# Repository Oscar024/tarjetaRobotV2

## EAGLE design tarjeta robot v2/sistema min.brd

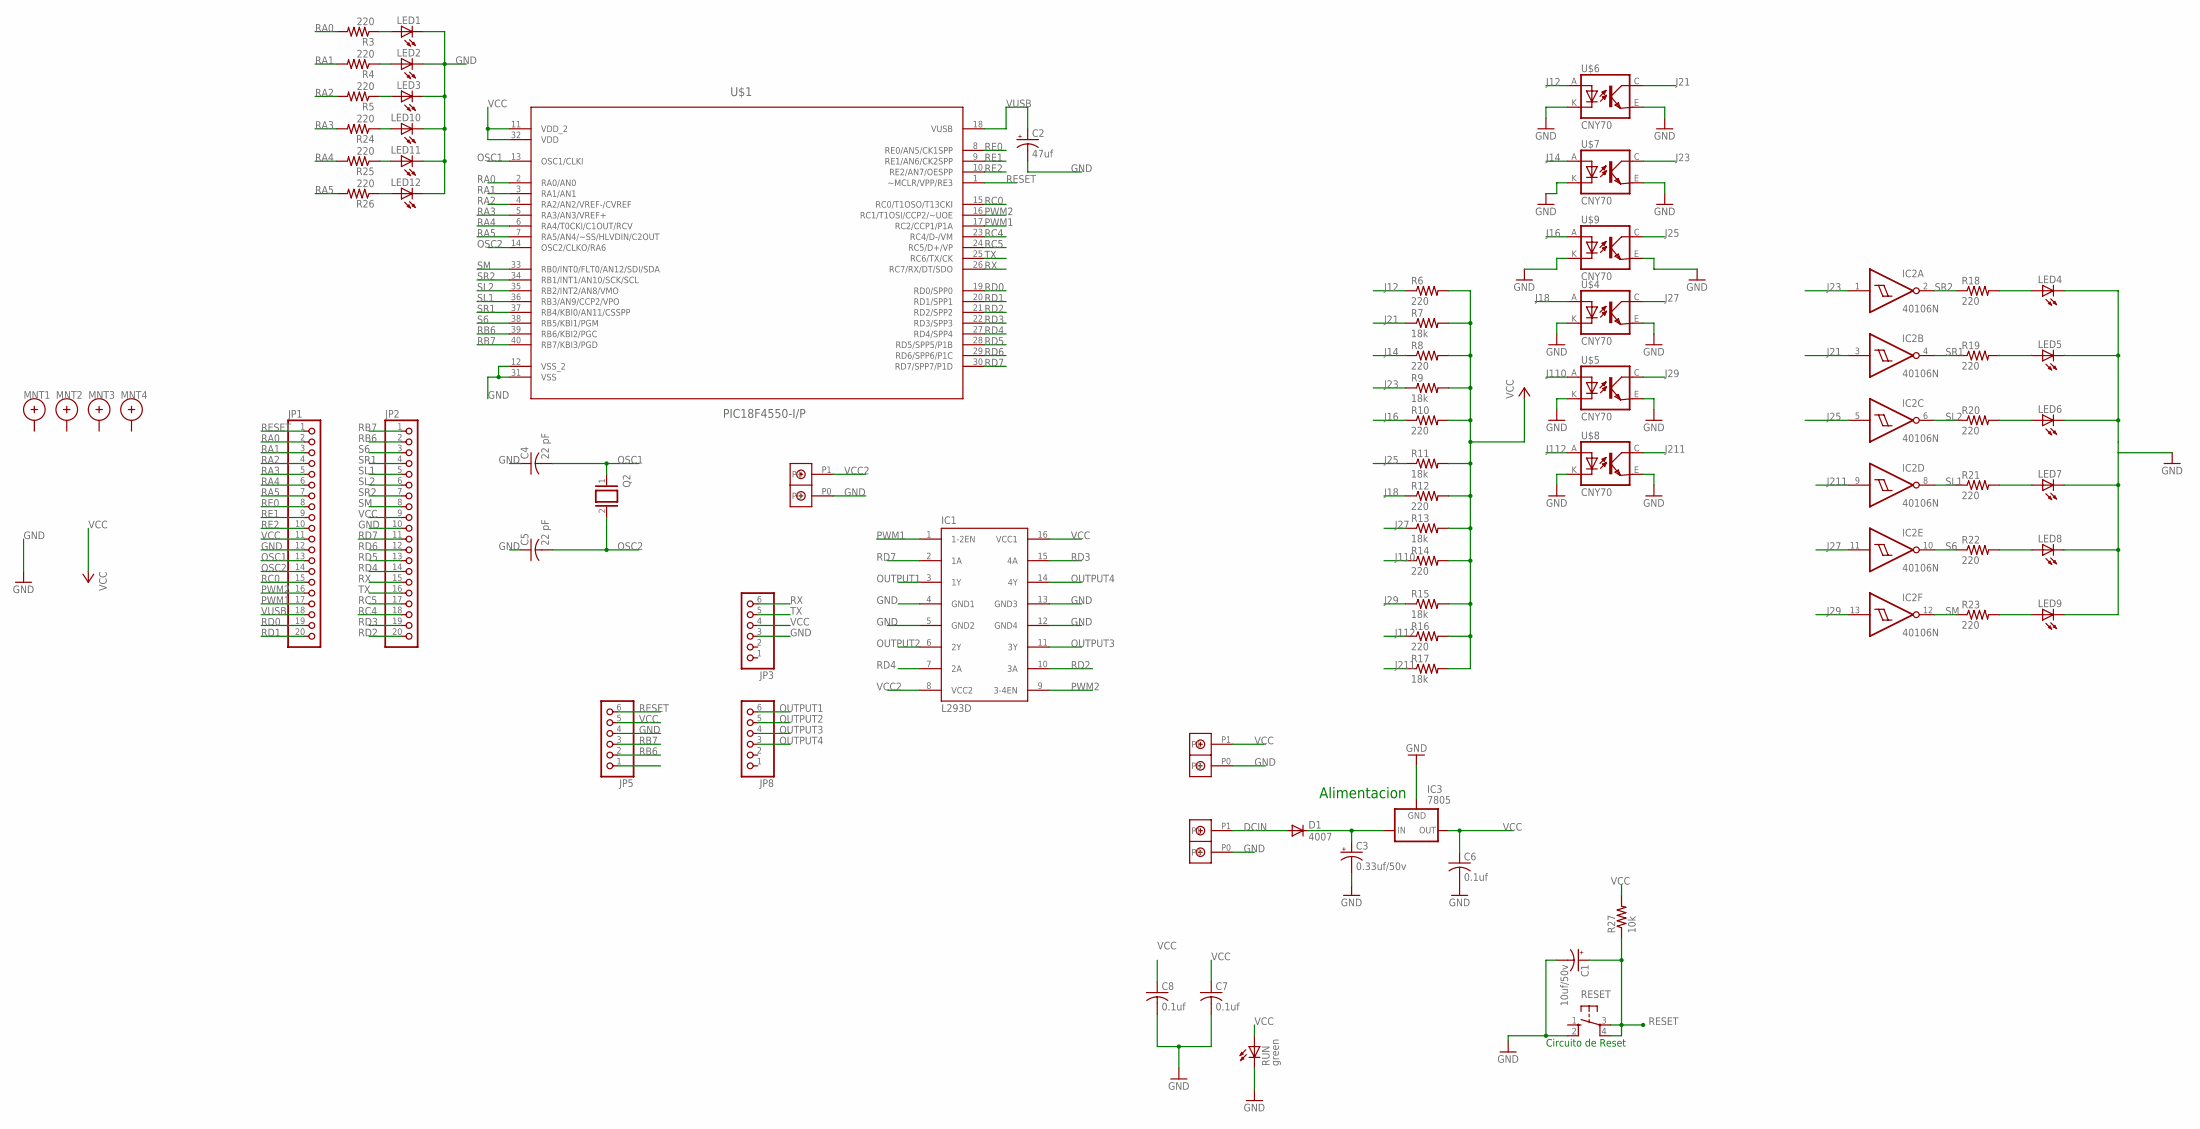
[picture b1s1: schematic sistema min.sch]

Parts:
C1: 10uf/50v; 153CLV-0505
C2: 47uf; 153CLV-0605
C3: 0.33uf/50v; 153CLV-0405
C4, C5: 22 pF; C1206
C6, C7, C8: 0.1uf; C1206
D1: 4007; DO35-7
IC1: L293D; DIL16
IC2: 40106N; DIL14
IC3: 7805; 79XXS
JP1, JP2: PINHD-1X20; 1X20
JP3, JP5, JP8: PINHD-1X6; 1X06
LED1, LED2, LED3, LED4, LED5, LED6, LED7, LED8, LED9, LED10, LED11, LED12: LEDCHIPLED_1206; CHIPLED_1206
MNT1, MNT2, MNT3, MNT4: HOLE_MNT_0.135; HOLE_MNT_#5-40
Q2: XTAL/S; QS
R3, R4, R5, R6, R8, R10, R12, R14, R16, R18, R19, R20, R21, R22, R23, R24, R25, R26: 220; M1206
R7, R9, R11, R13, R15, R17: 18k; M1206
R27: 10k; R1206
RESET: B3F-10XX
RUN: green; SML1206
U$1: PIC18F4550-I/P; DIP254P1524X635-40
U$2, U$3, U$10: DBCONN-1X2
U$4, U$5, U$6, U$7, U$8, U$9: CNY70; 4

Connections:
DCIN: D1.A, U$2.P1
GND: C1.-, C2.-, C3.-, C4.1, C5.1, C6.2, C7.2, C8.2, IC1.4 (GND1), IC1.5 (GND2), IC1.12 (GND4), IC1.13 (GND3), IC3.GND, JP1.12, JP2.10, JP3.3, JP5.4, LED1.C, LED2.C, LED3.C, LED4.C, LED5.C, LED6.C, LED7.C, LED8.C, LED9.C, LED10.C, LED11.C, LED12.C, RESET.2 (S1), RUN.C, U$1.12 (VSS_2), U$1.31 (VSS), U$2.P0, U$3.P0, U$4.E (EMI), U$4.K (C), U$5.E (EMI), U$5.K (C), U$6.E (EMI), U$6.K (C), U$7.E (EMI), U$7.K (C), U$8.E (EMI), U$8.K (C), U$9.E (EMI), U$9.K (C), U$10.P0
J12: R6.1, U$6.A
J14: R8.1, U$7.A
J16: R10.1, U$9.A
J18: R12.1, U$4.A
J21: IC2.3 (I), R7.1, U$6.C (COL)
J23: IC2.1 (I), R9.1, U$7.C (COL)
J25: IC2.5 (I), R11.1, U$9.C (COL)
J27: IC2.11 (I), R13.1, U$4.C (COL)
J29: IC2.13 (I), R15.1, U$5.C (COL)
J110: R14.1, U$5.A
J112: R16.1, U$8.A
J211: IC2.9 (I), R17.1, U$8.C (COL)
unnamed: LED4.A, R18.2
unnamed: LED10.A, R24.1
unnamed: LED1.A, R3.1
unnamed: LED11.A, R25.1
unnamed: LED2.A, R4.1
unnamed: LED3.A, R5.1
unnamed: LED12.A, R26.1
unnamed: LED5.A, R19.2
unnamed: LED6.A, R20.2
unnamed: LED7.A, R21.2
unnamed: LED8.A, R22.2
unnamed: LED9.A, R23.2
unnamed: C3.+, D1.C, IC3.IN
OSC1: C4.2, JP1.13, Q2.1, U$1.13 (OSC1/CLKI)
OSC2: C5.2, JP1.14, Q2.2, U$1.14 (OSC2/CLKO/RA6)
OUTPUT1: IC1.3 (1Y), JP8.6
OUTPUT2: IC1.6 (2Y), JP8.5
OUTPUT3: IC1.11 (3Y), JP8.4
OUTPUT4: IC1.14 (4Y), JP8.3
PWM1: IC1.1 (1-2EN), JP1.17, U$1.17 (RC2/CCP1/P1A)
PWM2: IC1.9 (3-4EN), JP1.16, U$1.16 (RC1/T1OSI/CCP2/~UOE)
RA0: JP1.2, R3.2, U$1.2 (RA0/AN0)
RA1: JP1.3, R4.2, U$1.3 (RA1/AN1)
RA2: JP1.4, R5.2, U$1.4 (RA2/AN2/VREF-/CVREF)
RA3: JP1.5, R24.2, U$1.5 (RA3/AN3/VREF+)
RA4: JP1.6, R25.2, U$1.6 (RA4/T0CKI/C1OUT/RCV)
RA5: JP1.7, R26.2, U$1.7 (RA5/AN4/~SS/HLVDIN/C2OUT)
RB6: JP2.2, JP5.2, U$1.39 (RB6/KBI2/PGC)
RB7: JP2.1, JP5.3, U$1.40 (RB7/KBI3/PGD)
RC0: JP1.15, U$1.15 (RC0/T1OSO/T13CKI)
RC4: JP2.18, U$1.23 (RC4/D-/VM)
RC5: JP2.17, U$1.24 (RC5/D+/VP)
RD0: JP1.19, U$1.19 (RD0/SPP0)
RD1: JP1.20, U$1.20 (RD1/SPP1)
RD2: IC1.10 (3A), JP2.20, U$1.21 (RD2/SPP2)
RD3: IC1.15 (4A), JP2.19, U$1.22 (RD3/SPP3)
RD4: IC1.7 (2A), JP2.14, U$1.27 (RD4/SPP4)
RD5: JP2.13, U$1.28 (RD5/SPP5/P1B)
RD6: JP2.12, U$1.29 (RD6/SPP6/P1C)
RD7: IC1.2 (1A), JP2.11, U$1.30 (RD7/SPP7/P1D)
RE0: JP1.8, U$1.8 (RE0/AN5/CK1SPP)
RE1: JP1.9, U$1.9 (RE1/AN6/CK2SPP)
RE2: JP1.10, U$1.10 (RE2/AN7/OESPP)
RESET: C1.+, JP1.1, JP5.6, R27.1, RESET.3, RESET.4 (P1), U$1.1 (~MCLR/VPP/RE3)
RX: JP2.15, JP3.6, U$1.26 (RC7/RX/DT/SDO)
S6: IC2.10 (O), JP2.3, R22.1, U$1.38 (RB5/KBI1/PGM)
SL1: IC2.8 (O), JP2.5, R21.1, U$1.36 (RB3/AN9/CCP2/VPO)
SL2: IC2.6 (O), JP2.6, R20.1, U$1.35 (RB2/INT2/AN8/VMO)
SM: IC2.12 (O), JP2.8, R23.1, U$1.33 (RB0/INT0/FLT0/AN12/SDI/SDA)
SR1: IC2.4 (O), JP2.4, R19.1, U$1.37 (RB4/KBI0/AN11/CSSPP)
SR2: IC2.2 (O), JP2.7, R18.1, U$1.34 (RB1/INT1/AN10/SCK/SCL)
TX: JP2.16, JP3.5, U$1.25 (RC6/TX/CK)
VCC: C6.1, C7.1, C8.1, IC1.16 (VCC1), IC3.OUT, JP1.11, JP2.9, JP3.4, JP5.5, R6.2, R7.2, R8.2, R9.2, R10.2, R11.2, R12.2, R13.2, R14.2, R15.2, R16.2, R17.2, R27.2, RUN.A, U$1.11 (VDD_2), U$1.32 (VDD), U$10.P1
VCC2: IC1.8 (VCC2), U$3.P1
VDD: IC2.14 (VDD)
VSS: IC2.7 (VSS)
VUSB: C2.+, JP1.18, U$1.18 (VUSB)

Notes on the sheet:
Alimentacion
Circuito de Reset

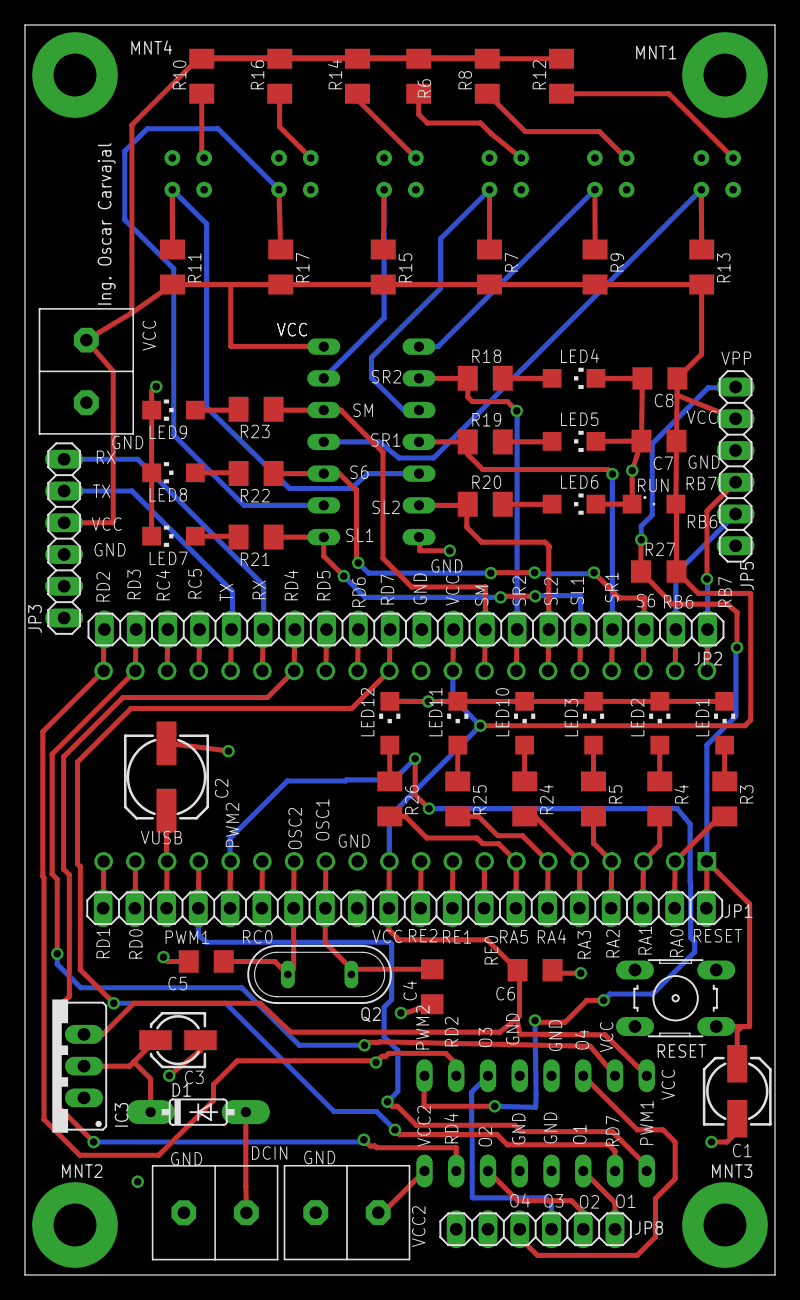
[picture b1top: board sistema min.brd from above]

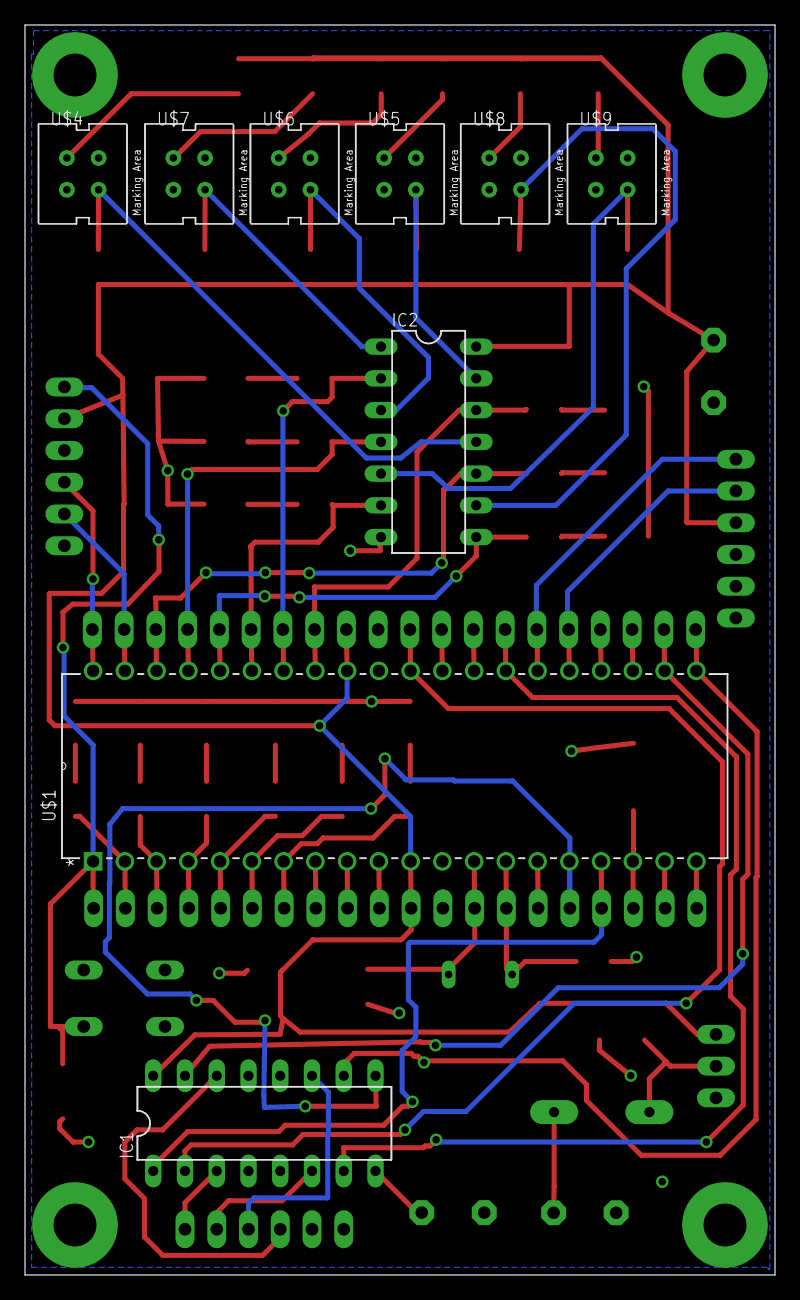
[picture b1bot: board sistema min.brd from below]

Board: 2 copper layers, 60.0 x 100.0 mm, 71 parts (9 on the bottom side), 69 nets.
